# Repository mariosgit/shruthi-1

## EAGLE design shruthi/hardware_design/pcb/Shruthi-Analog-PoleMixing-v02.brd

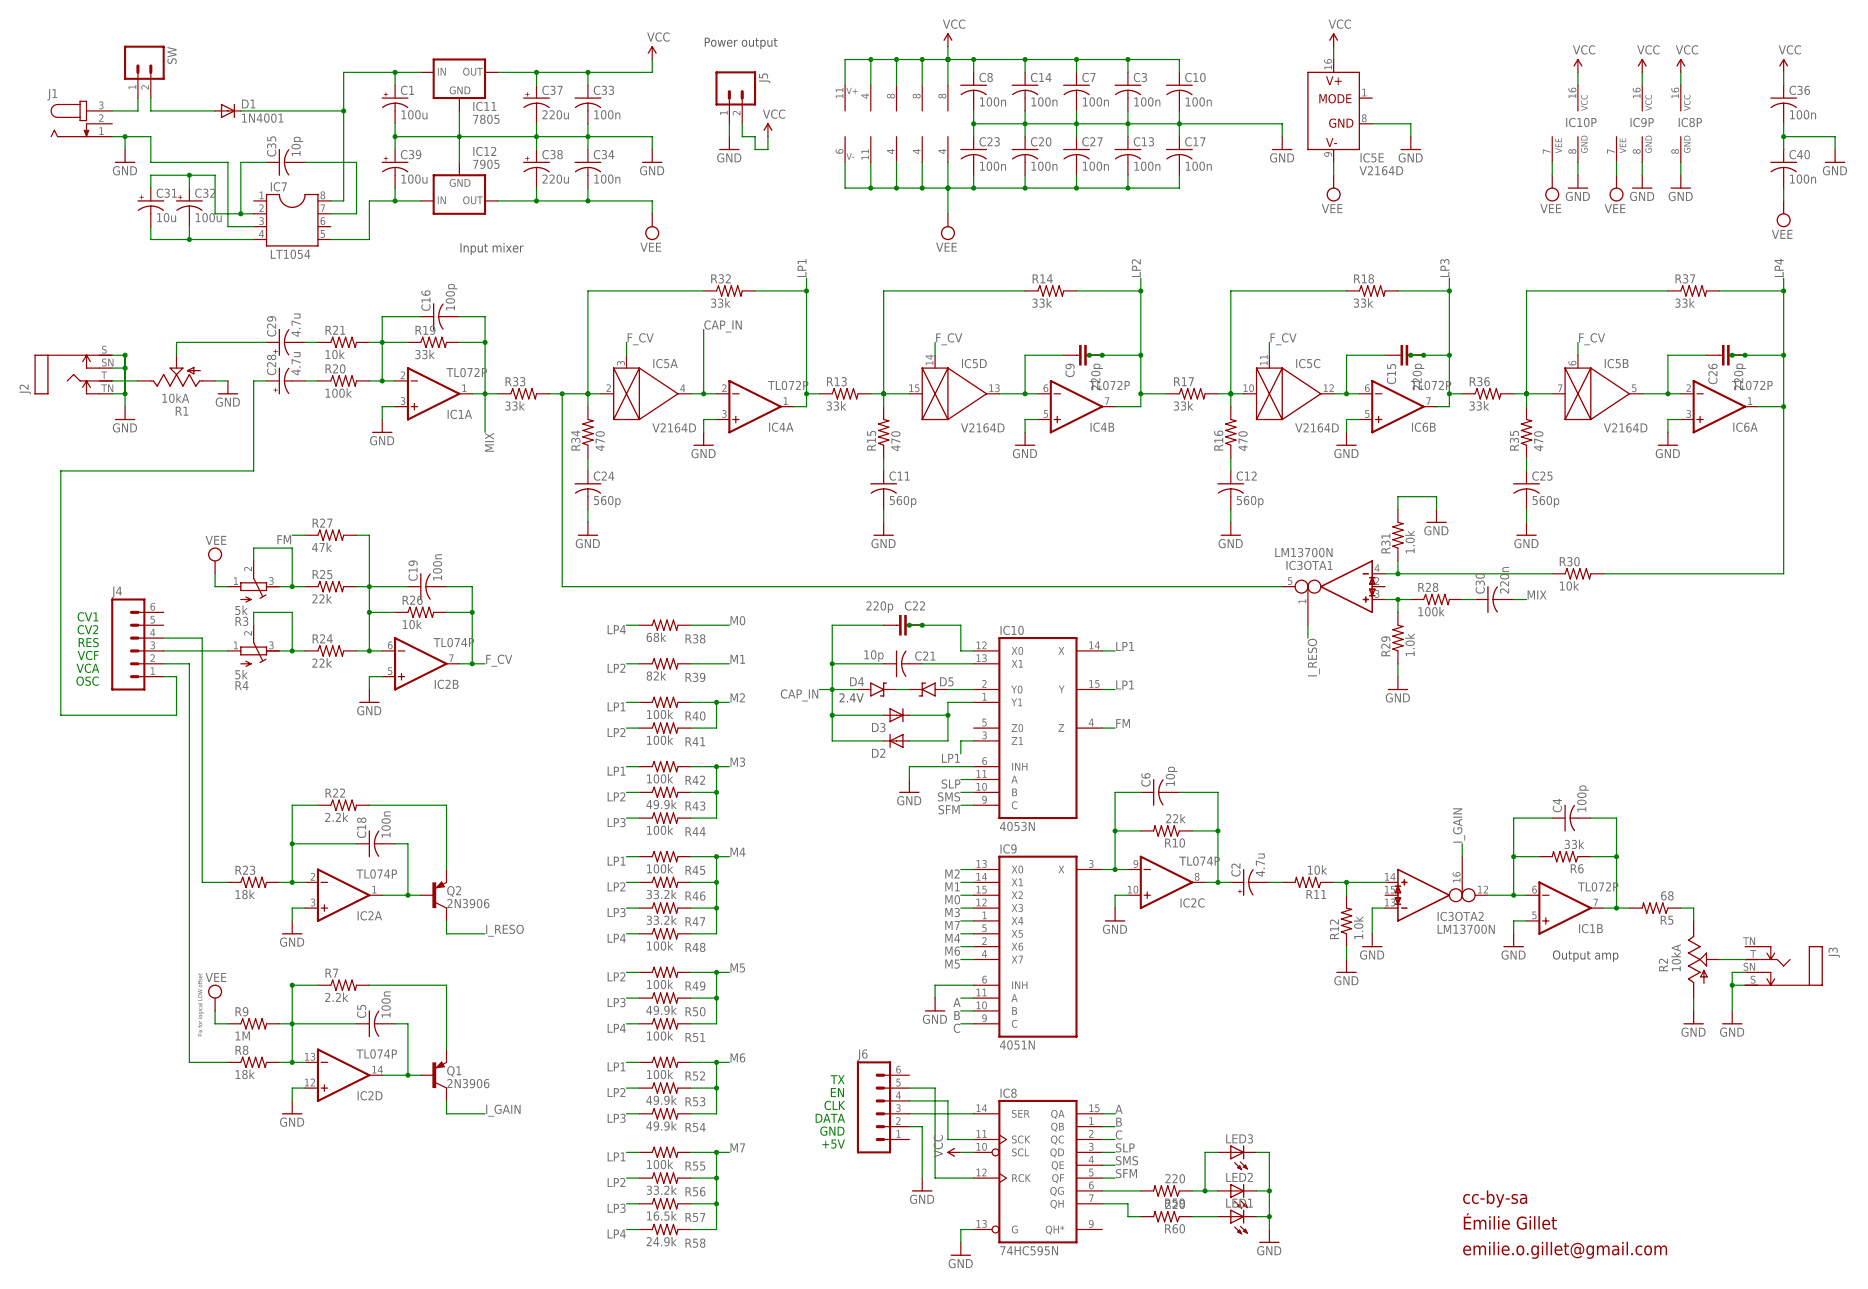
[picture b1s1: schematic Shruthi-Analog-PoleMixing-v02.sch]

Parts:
C1, C39: 100u; E2,5-7
C2, C28, C29: 4.7u; E2,5-6
C3, C5, C7, C8, C10, C13, C14, C17, C18, C19, C20, C23, C27, C33, C34, C36, C40: 100n; C025-025X050
C4, C16: 100p; C025-025X050
C6, C21, C35: 10p; C025-025X050
C9, C15, C22, C26: 220p; C2.5/5-4
C11, C12, C24, C25: 560p; C025-025X050
C30: 220n; C025-025X050
C31: 10u; E2,5-5
C32: 100u; E2,5-6
C37, C38: 220u; E5-10,5
D1: 1N4001; DO41-10
D2, D3: DIODE-D-5; D-5
D4, D5: 1N47XXDO35; D-5
IC1, IC4, IC6: TL072P; DIL08
IC2: TL074P; DIL14
IC3: LM13700N; DIL16
IC5: V2164D; DIL16
IC7: LT1054; DIL08
IC8: 74HC595N; DIL16
IC9: 4051N; DIL16
IC10: 4053N; DIL16
IC11: 7805; 78XXS
IC12: 7905; 79XXS
J1: JACK-PLUG2; SPC4078_BIG_HOLES
J2, J3: MONOSWS; NMJ4HC-S
J4, J6: M06SIP; 1X06
J5: M02PTH; 1X02
LED1, LED2: LED3MM
LED3: LEDCHIP-LED0603; CHIP-LED0603
Q1, Q2: 2N3906; TO92-
R1, R2: 10kA; CABLE_POT_6MM
R3, R4: 5k; RTRIM3296X
R5: 68; 0204/7
R6, R13, R14, R17, R18, R19, R32, R33, R36, R37: 33k; 0204/7
R7, R22: 2.2k; 0204/7
R8, R23: 18k; 0204/7
R9: 1M; 0204/7
R10, R24, R25: 22k; 0204/7
R11, R21, R26, R30: 10k; 0204/7
R12, R29, R31: 1.0k; 0204/7
R15, R16, R34, R35: 470; 0204/7
R20, R28, R40, R41, R42, R44, R45, R48, R49, R51, R52, R55: 100k; 0204/7
R27: 47k; 0204/7
R38: 68k; 0204/7
R39: 82k; 0204/7
R43, R50, R53, R54: 49.9k; 0204/7
R46, R47, R56: 33.2k; 0204/7
R57: 16.5k; 0204/7
R58: 24.9k; 0204/7
R59, R60: 220; 0204/7
SW: M02PTH; 1X02

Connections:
A: IC8.15 (QA), IC9.11 (A)
B: IC8.1 (QB), IC9.10 (B)
C: IC8.2 (QC), IC9.9 (C)
CAP_IN: C21.1, C22.1, D2.C, D3.A, D4.A, IC4.2 (-IN), IC5.4 (OUT)
FM: IC10.4 (Z), R27.1
F_CV: C19.2, IC2.7 (OUT), IC5.3 (CTRL), IC5.6 (CTRL), IC5.11 (CTRL), IC5.14 (CTRL), R26.2
GND: C1.-, C3.2, C7.2, C8.2, C10.2, C11.2, C12.2, C13.1, C14.2, C17.1, C20.1, C23.1, C24.2, C25.2, C27.1, C33.2, C34.1, C36.2, C37.-, C38.+, C39.+, C40.1, IC1.3 (+IN), IC1.5 (+IN), IC2.3 (+IN), IC2.5 (+IN), IC2.10 (+IN), IC2.12 (+IN), IC3.13 (IN_N), IC4.3 (+IN), IC4.5 (+IN), IC5.8 (GND), IC6.3 (+IN), IC6.5 (+IN), IC7.3, IC8.8 (GND), IC8.13 (G), IC9.6 (INH), IC9.8 (GND), IC10.6 (INH), IC10.8 (GND), IC11.GND, IC12.GND, J1.1, J2.S, J2.SN, J2.TN, J3.S, J3.SN, J5.1, J6.2, LED1.K (C), LED2.K (C), LED3.C, R1.A, R2.A, R12.1, R29.1, R31.2
I_GAIN: IC3.16 (I_BIAS), Q1.1 (C)
I_RESO: IC3.1 (I_BIAS), Q2.1 (C)
LP1: IC4.1 (OUT), IC10.3 (Z1), IC10.14 (X), IC10.15 (Y), R13.1, R32.2, R40.1, R42.1, R45.1, R52.1, R55.1
LP2: C9.2, C9.3, IC4.7 (OUT), R14.2, R17.1, R39.1, R41.1, R43.1, R46.1, R49.1, R53.1, R56.1
LP3: C15.2, C15.3, IC6.7 (OUT), R18.2, R36.1, R44.1, R47.1, R50.1, R54.1, R57.1
LP4: C26.2, C26.3, IC6.1 (OUT), R30.2, R37.2, R38.1, R48.1, R51.1, R58.1
M0: IC9.15 (X2), R38.2
M1: IC9.14 (X1), R39.2
M2: IC9.13 (X0), R40.2, R41.2
M3: IC9.12 (X3), R42.2, R43.2, R44.2
M4: IC9.5 (X5), R45.2, R46.2, R47.2, R48.2
M5: IC9.4 (X7), R49.2, R50.2, R51.2
M6: IC9.2 (X6), R52.2, R53.2, R54.2
M7: IC9.1 (X4), R55.2, R56.2, R57.2, R58.2
MIX: C16.2, C30.2, IC1.1 (OUT), R19.2, R33.1
unnamed: C9.1, IC4.6 (-IN), IC5.13 (OUT)
unnamed: C15.1, IC5.12 (OUT), IC6.6 (-IN)
unnamed: IC5.10 (IN), R16.2, R17.2, R18.1
unnamed: C12.1, R16.1
unnamed: C25.1, R35.1
unnamed: C16.1, IC1.2 (-IN), R19.1, R20.2, R21.2
unnamed: IC5.7 (IN), R35.2, R36.2, R37.1
unnamed: C26.1, IC5.5 (OUT), IC6.2 (-IN)
unnamed: C18.2, IC2.1 (OUT), Q2.2 (B)
unnamed: C19.1, IC2.6 (-IN), R24.2, R25.2, R26.1, R27.2
unnamed: R4.2 (S), R4.3 (A), R24.1
unnamed: J4.3, R4.1 (E)
unnamed: J3.T, R2.S
unnamed: IC8.12 (RCK), J6.5
unnamed: C5.2, IC2.14 (OUT), Q1.2 (B)
unnamed: IC3.14 (IN_P), R11.1, R12.2
unnamed: J4.4, R23.1
unnamed: C2.-, R11.2
unnamed: IC3.4 (IN_N), R30.1, R31.1
unnamed: IC3.3 (IN_P), R28.1, R29.2
unnamed: C30.1, R28.2
unnamed: R3.2 (S), R3.3 (A), R25.1
unnamed: D4.C, D5.C
unnamed: R2.E, R5.1
unnamed: C11.1, R15.1
unnamed: C21.2, IC10.13 (X1)
unnamed: IC8.6 (QG), R59.2
unnamed: IC8.11 (SCK), J6.4
unnamed: IC8.14 (SER), J6.3
unnamed: C22.2, C22.3, IC10.12 (X0)
unnamed: IC8.7 (QH), R60.2
unnamed: IC3.5 (OUT), IC5.2 (IN), R32.1, R33.2, R34.2
unnamed: C6.1, IC2.9 (-IN), IC9.3 (X), R10.2
unnamed: C28.+, J4.1
unnamed: C2.+, C6.2, IC2.8 (OUT), R10.1
unnamed: J2.T, R1.E
unnamed: C28.-, R20.1
unnamed: C24.1, R34.1
unnamed: LED2.A, LED3.A, R59.1
unnamed: LED1.A, R60.1
unnamed: IC5.15 (IN), R13.2, R14.1, R15.2
unnamed: J1.3, SW.1
unnamed: J4.2, R8.1
unnamed: C1.+, D1.C, IC7.8, IC11.IN
unnamed: C31.+, C32.+, C35.1, IC7.2
unnamed: C31.-, C32.-, IC7.4
unnamed: C35.2, IC7.7
unnamed: D2.A, D3.C, IC10.1 (Y1)
unnamed: C5.1, IC2.13 (-IN), R7.1, R8.2, R9.2
unnamed: D5.A, IC10.2 (Y0)
unnamed: C18.1, IC2.2 (-IN), R22.1, R23.2
unnamed: C39.-, IC7.5, IC12.IN
unnamed: D1.A, SW.2
unnamed: Q2.3 (E), R22.2
unnamed: C4.2, IC1.7 (OUT), R5.2, R6.1
unnamed: C29.+, R1.S
unnamed: Q1.3 (E), R7.2
unnamed: C4.1, IC1.6 (-IN), IC3.12 (OUT), R6.2
unnamed: C29.-, R21.1
SFM: IC8.5 (QF), IC10.9 (C)
SLP: IC8.3 (QD), IC10.11 (A)
SMS: IC8.4 (QE), IC10.10 (B)
VCC: C3.1, C7.1, C8.1, C10.1, C14.1, C33.1, C36.1, C37.+, IC1.8 (V+), IC2.4 (V+), IC3.11 (V+), IC4.8 (V+), IC5.16 (V+), IC6.8 (V+), IC8.10 (SCL), IC8.16 (VCC), IC9.16 (VCC), IC10.16 (VCC), IC11.OUT, J5.2
VEE: C13.2, C17.2, C20.2, C23.2, C27.2, C34.2, C38.-, C40.2, IC1.4 (V-), IC2.11 (V-), IC3.6 (V-), IC4.4 (V-), IC5.9 (V-), IC6.4 (V-), IC9.7 (VEE), IC10.7 (VEE), IC12.OUT, R3.1 (E), R9.1

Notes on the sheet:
Power output
OSC
VCA
VCF
RES
cc-by-sa
Output amp
CV1
CV2
Input mixer
+5V
GND
DATA
CLK
Fix for logical LOW offset
2.4V
Émilie Gillet
emilie.o.gillet@gmail.com

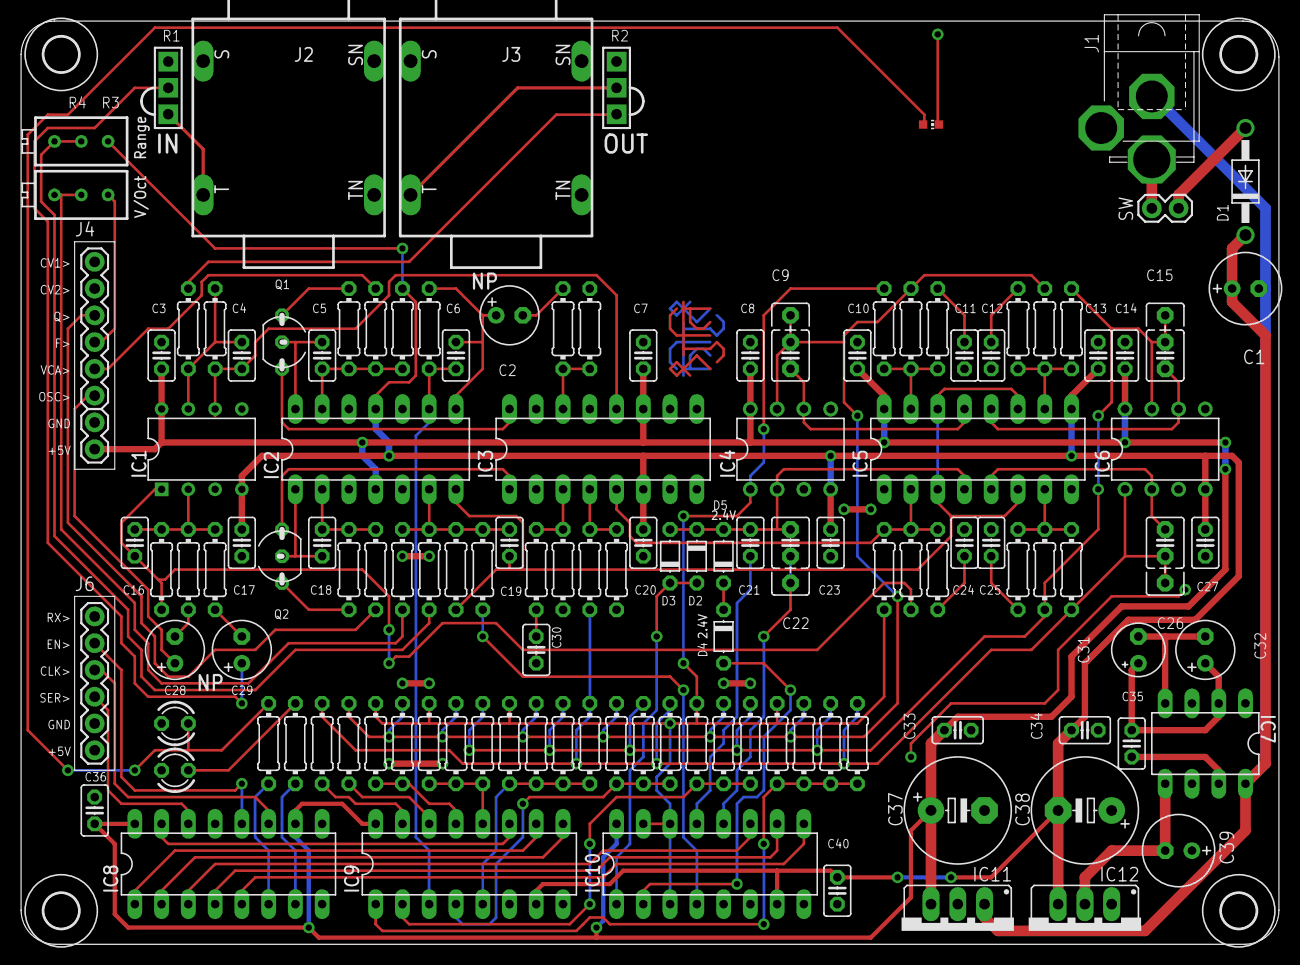
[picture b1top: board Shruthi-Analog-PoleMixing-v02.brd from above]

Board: 2 copper layers, 119.4 x 87.6 mm, 134 parts (0 on the bottom side), 86 nets.

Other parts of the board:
U$1, U$2, U$4, U$5: 3,3
U$3: 4POLE_MISSION

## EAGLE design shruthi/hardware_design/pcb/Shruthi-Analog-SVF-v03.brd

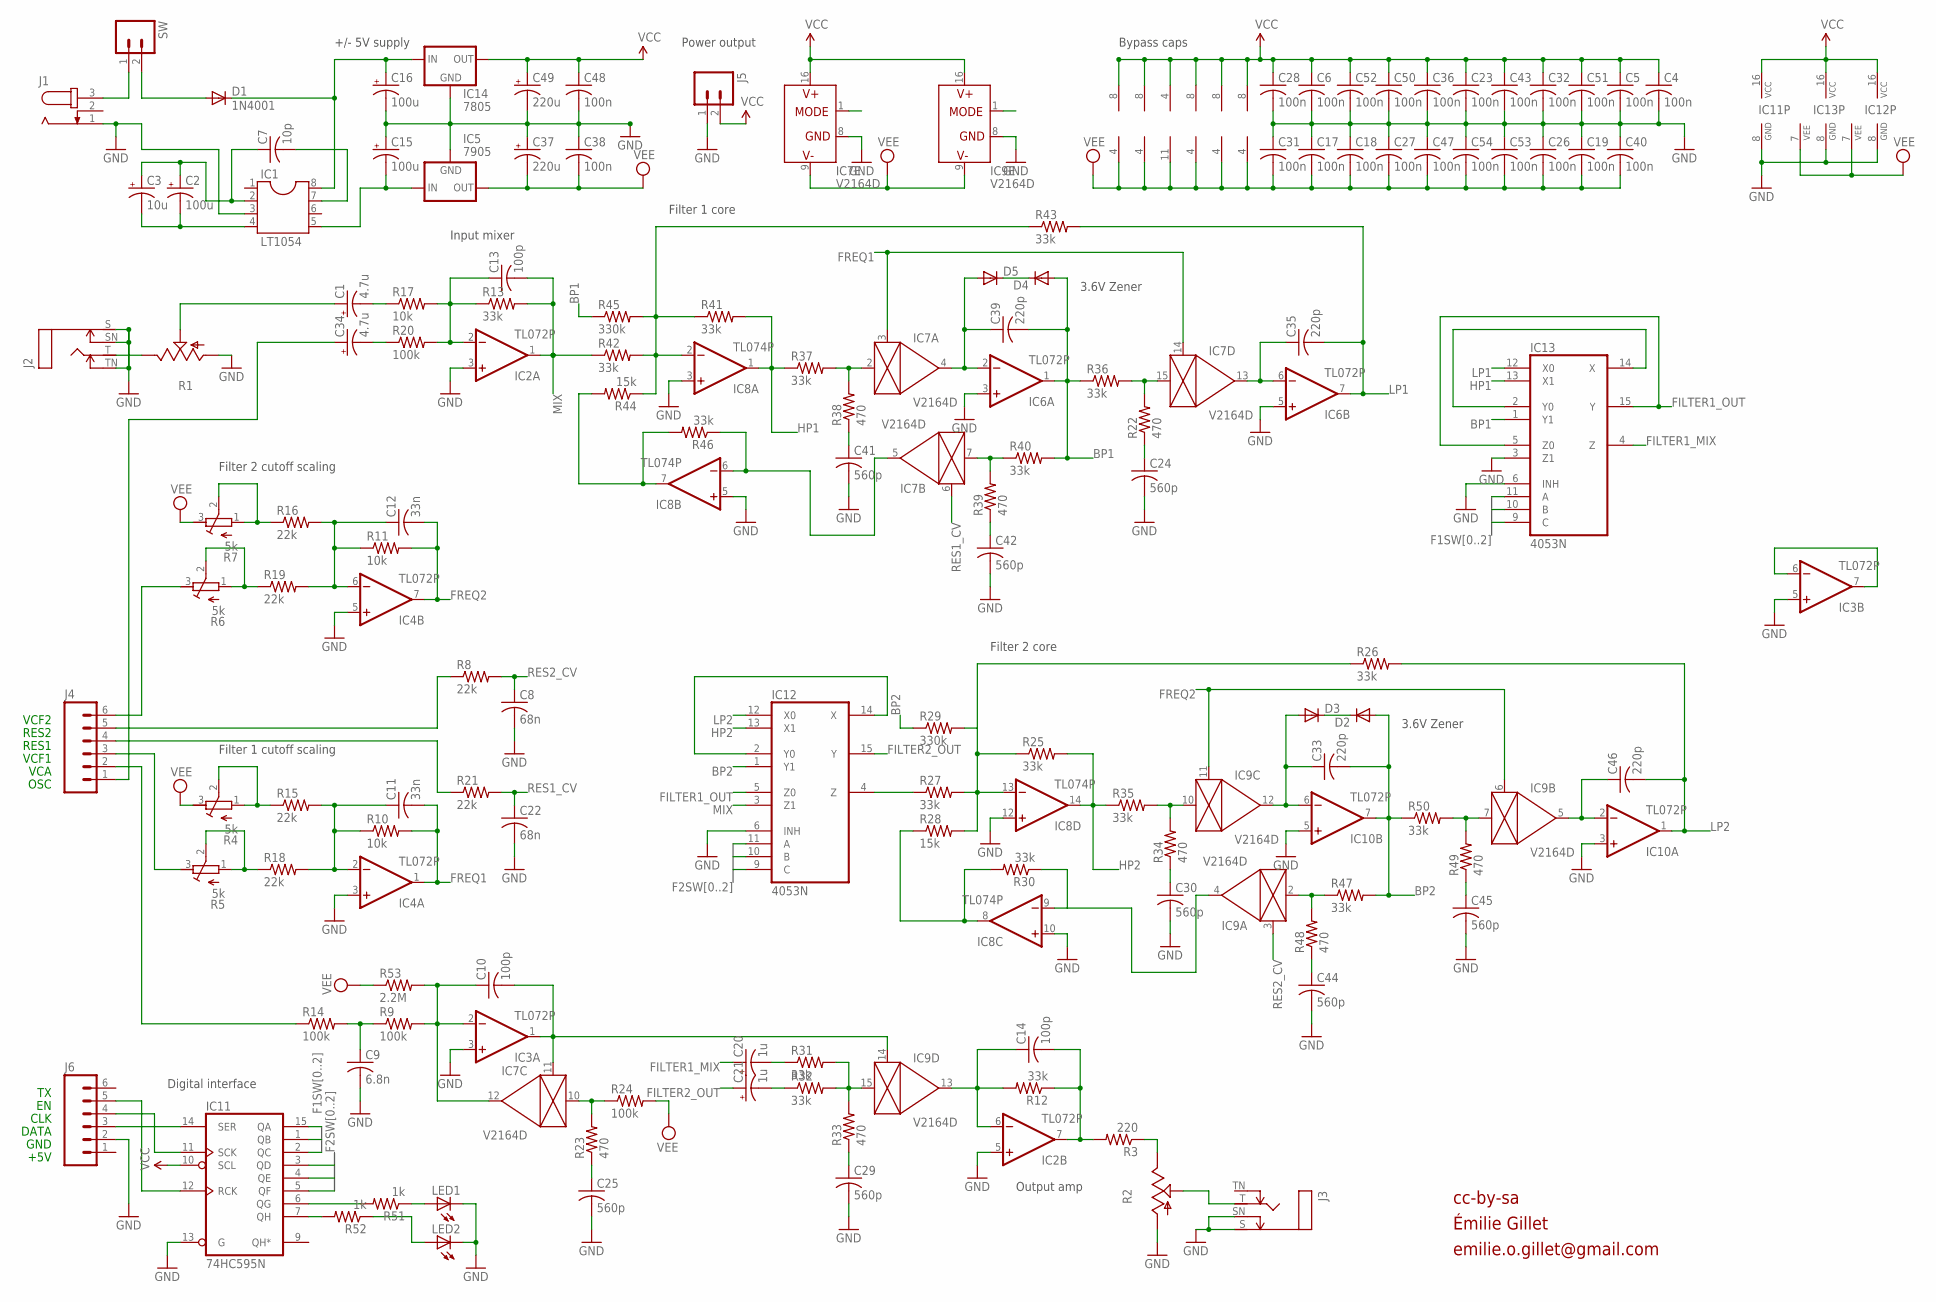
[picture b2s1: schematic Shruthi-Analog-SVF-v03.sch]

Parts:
C1, C34: 4.7u; E2,5-6
C2: 100u; E2,5-6
C3: 10u; E2,5-5
C4, C5, C6, C17, C18, C19, C23, C26, C27, C28, C31, C32, C36, C38, C40, C43, C47, C48, C50, C51, C52, C53, C54: 100n; C025-025X050
C7: 10p; C025-025X050
C8, C22: 68n; C050-025X075
C9: 6.8n; C025-025X050
C10, C13, C14: 100p; C025-025X050
C11, C12: 33n; C050-025X075
C15, C16: 100u; E2,5-7
C20, C21: 1u; E2-5
C24, C25, C29, C30, C41, C42, C44, C45: 560p; C025-025X050
C33, C35, C39, C46: 220p; C025-025X050
C37, C49: 220u; E5-10,5
D1: 1N4001; DO41-10
D2, D3, D4, D5: DIODE-D-5; D-5
IC1: LT1054; DIL08
IC2, IC3, IC4, IC6, IC10: TL072P; DIL08
IC5: 7905; 79XXS
IC7, IC9: V2164D; DIL16
IC8: TL074P; DIL14
IC11: 74HC595N; DIL16
IC12, IC13: 4053N; DIL16
IC14: 7805; 78XXS
J1: JACK-PLUG2; SPC4078_BIG_HOLES
J2, J3: MONOSWS; NMJ4HC-S
J4, J6: M06SIP; 1X06
J5: M02PTH; 1X02
LED1, LED2: LEDCHIP-LED0603; CHIP-LED0603
R1, R2: POT_USCABLED; CABLE_POT_6MM
R3: 220; 0204/7
R4, R5, R6, R7: 5k; RTRIM3296X
R8, R15, R16, R18, R19, R21: 22k; 0204/7
R9, R14, R20, R24: 100k; 0204/7
R10, R11, R17: 10k; 0204/7
R12, R13, R25, R26, R27, R30, R31, R32, R35, R36, R37, R40, R41, R42, R43, R46, R47, R50: 33k; 0204/7
R22, R23, R33, R34, R38, R39, R48, R49: 470; 0204/7
R28, R44: 15k; 0204/7
R29, R45: 330k; 0204/7
R51, R52: 1k; 0204/7
R53: 2.2M; 0204V
SW: M02PTH; 1X02

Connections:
BP1: C39.2, D4.A, IC6.1 (OUT), IC13.1 (Y1), R36.1, R40.2, R45.1
BP2: C33.2, D2.A, IC10.7 (OUT), IC12.1 (Y1), R29.1, R47.2, R50.1
F1SW0: IC11.15 (QA), IC13.9 (C)
F1SW1: IC11.1 (QB), IC13.10 (B)
F1SW2: IC11.2 (QC), IC13.11 (A)
F2SW0: IC11.3 (QD), IC12.9 (C)
F2SW1: IC11.4 (QE), IC12.10 (B)
F2SW2: IC11.5 (QF), IC12.11 (A)
FILTER1_MIX: C20.+, IC13.4 (Z)
FILTER1_OUT: IC12.5 (Z0), IC13.5 (Z0), IC13.15 (Y)
FILTER2_OUT: C21.+, IC12.15 (Y)
FREQ1: C11.2, IC4.1 (OUT), IC7.3 (CTRL), IC7.14 (CTRL), R10.2
FREQ2: C12.2, IC4.7 (OUT), IC9.6 (CTRL), IC9.11 (CTRL), R11.2
GND: C4.2, C5.2, C6.2, C8.2, C9.2, C15.+, C16.-, C17.1, C18.1, C19.1, C22.2, C23.2, C24.2, C25.2, C26.1, C27.1, C28.2, C29.2, C30.2, C31.1, C32.2, C36.2, C37.+, C38.1, C40.1, C41.2, C42.2, C43.2, C44.2, C45.2, C47.1, C48.2, C49.-, C50.2, C51.2, C52.2, C53.1, C54.1, IC1.3, IC2.3 (+IN), IC2.5 (+IN), IC3.3 (+IN), IC3.5 (+IN), IC4.3 (+IN), IC4.5 (+IN), IC5.GND, IC6.3 (+IN), IC6.5 (+IN), IC7.8 (GND), IC8.3 (+IN), IC8.5 (+IN), IC8.10 (+IN), IC8.12 (+IN), IC9.8 (GND), IC10.3 (+IN), IC10.5 (+IN), IC11.8 (GND), IC11.13 (G), IC12.6 (INH), IC12.8 (GND), IC13.3 (Z1), IC13.6 (INH), IC13.8 (GND), IC14.GND, J1.1, J2.S, J2.SN, J2.TN, J3.S, J3.SN, J5.1, J6.2, LED1.C, LED2.C, R1.A, R2.A
HP1: IC8.1 (OUT), IC13.13 (X1), R37.1, R41.2
HP2: IC8.14 (OUT), IC12.13 (X1), R25.2, R35.1
LP1: C35.2, IC6.7 (OUT), IC13.12 (X0), R43.2
LP2: C46.2, IC10.1 (OUT), IC12.12 (X0), R26.2
MIX: C13.2, IC2.1 (OUT), IC12.3 (Z1), R13.2, R42.1
unnamed: C2.+, C3.+, C7.1, IC1.2
unnamed: C12.1, IC4.6 (-IN), R11.1, R16.2, R19.2
unnamed: J1.3, SW.1
unnamed: C16.+, D1.C, IC1.8, IC14.IN
unnamed: C2.-, C3.-, IC1.4
unnamed: C13.1, IC2.2 (-IN), R13.1, R17.2, R20.2
unnamed: R6.1 (E), R6.2 (S), R19.1
unnamed: J4.6, R6.3 (A)
unnamed: R7.1 (E), R7.2 (S), R16.1
unnamed: IC7.10 (IN), R23.2, R24.1
unnamed: C10.1, IC3.2 (-IN), IC7.12 (OUT), R9.2, R53.2
unnamed: IC8.2 (-IN), R41.1, R42.2, R43.1, R44.1, R45.2
unnamed: IC11.12 (RCK), J6.5
unnamed: IC11.14 (SER), J6.3
unnamed: IC11.6 (QG), R51.2
unnamed: IC11.11 (SCK), J6.4
unnamed: C24.1, R22.1
unnamed: IC8.13 (-IN), R25.1, R26.1, R27.2, R28.2, R29.2
unnamed: C39.1, D5.A, IC6.2 (-IN), IC7.4 (OUT)
unnamed: C33.1, D3.A, IC9.12 (OUT), IC10.6 (-IN)
unnamed: IC7.7 (IN), R39.2, R40.1
unnamed: C9.1, R9.1, R14.2
unnamed: IC8.8 (OUT), R28.1, R30.2
unnamed: IC9.2 (IN), R47.1, R48.2
unnamed: R2.E, R3.1
unnamed: IC7.15 (IN), R22.2, R36.2
unnamed: C42.1, R39.1
unnamed: C35.1, IC6.6 (-IN), IC7.13 (OUT)
unnamed: IC7.2 (IN), R37.2, R38.2
unnamed: C41.1, R38.1
unnamed: IC7.5 (OUT), IC8.6 (-IN), R46.1
unnamed: LED1.A, R51.1
unnamed: D2.C, D3.C
unnamed: IC9.7 (IN), R49.2, R50.2
unnamed: C34.+, J4.1
unnamed: C7.2, IC1.7
unnamed: IC8.9 (-IN), IC9.4 (OUT), R30.1
unnamed: J2.T, R1.E
unnamed: C34.-, R20.1
unnamed: C11.1, IC4.2 (-IN), R10.1, R15.2, R18.2
unnamed: R5.1 (E), R5.2 (S), R18.1
unnamed: J4.3, R5.3 (A)
unnamed: R4.1 (E), R4.2 (S), R15.1
unnamed: C46.1, IC9.5 (OUT), IC10.2 (-IN)
unnamed: J4.2, R14.1
unnamed: C45.1, R49.1
unnamed: J3.T, R2.S
unnamed: IC8.7 (OUT), R44.2, R46.2
unnamed: C44.1, R48.1
unnamed: IC9.10 (IN), R34.2, R35.2
unnamed: C30.1, R34.1
unnamed: LED2.A, R52.1
unnamed: IC11.7 (QH), R52.2
unnamed: D4.C, D5.C
unnamed: C10.2, IC3.1 (OUT), IC7.11 (CTRL), IC9.14 (CTRL)
unnamed: C20.-, R31.1
unnamed: C15.-, IC1.5, IC5.IN
unnamed: D1.A, SW.2
unnamed: C21.-, R32.1
unnamed: IC3.6 (-IN), IC3.7 (OUT)
unnamed: IC13.2 (Y0), IC13.14 (X)
unnamed: C14.2, IC2.7 (OUT), R3.2, R12.1
unnamed: C25.1, R23.1
unnamed: C29.1, R33.1
unnamed: C1.+, R1.S
unnamed: IC9.15 (IN), R31.2, R32.2, R33.2
unnamed: J4.4, R21.1
unnamed: C14.1, IC2.6 (-IN), IC9.13 (OUT), R12.2
unnamed: C1.-, R17.1
unnamed: J4.5, R8.1
unnamed: IC12.2 (Y0), IC12.14 (X)
unnamed: IC12.4 (Z), R27.1
RES1_CV: C22.1, IC7.6 (CTRL), R21.2
RES2_CV: C8.1, IC9.3 (CTRL), R8.2
VCC: C4.1, C5.1, C6.1, C23.1, C28.1, C32.1, C36.1, C43.1, C48.1, C49.+, C50.1, C51.1, C52.1, IC2.8 (V+), IC3.8 (V+), IC4.8 (V+), IC6.8 (V+), IC7.16 (V+), IC8.4 (V+), IC9.16 (V+), IC10.8 (V+), IC11.10 (SCL), IC11.16 (VCC), IC12.16 (VCC), IC13.16 (VCC), IC14.OUT, J5.2
VEE: C17.2, C18.2, C19.2, C26.2, C27.2, C31.2, C37.-, C38.2, C40.2, C47.2, C53.2, C54.2, IC2.4 (V-), IC3.4 (V-), IC4.4 (V-), IC5.OUT, IC6.4 (V-), IC7.9 (V-), IC8.11 (V-), IC9.9 (V-), IC10.4 (V-), IC12.7 (VEE), IC13.7 (VEE), R4.3 (A), R7.3 (A), R24.2, R53.1

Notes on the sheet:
Power output
OSC
VCA
VCF1
RES1
Input mixer
Filter 1 cutoff scaling
cc-by-sa
+/- 5V supply
Bypass caps
Output amp
VCF2
RES2
+5V
GND
DATA
CLK
Digital interface
Filter 2 cutoff scaling
Filter 1 core
Filter 2 core
3.6V Zener
Émilie Gillet
emilie.o.gillet@gmail.com

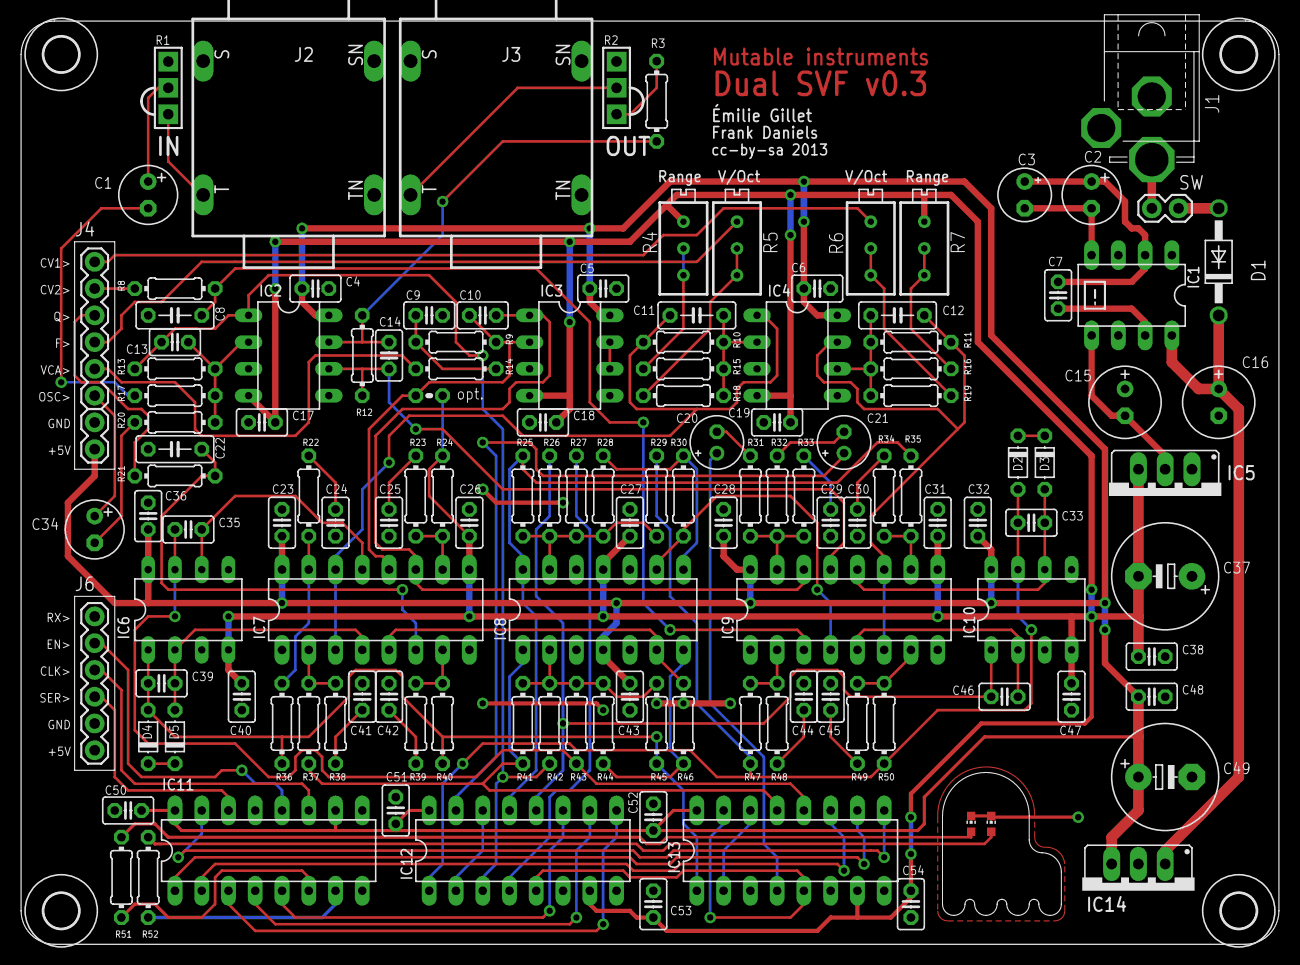
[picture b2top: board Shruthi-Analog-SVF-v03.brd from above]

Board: 2 copper layers, 119.4 x 87.6 mm, 139 parts (0 on the bottom side), 95 nets.

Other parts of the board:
U$1, U$2, U$3, U$4: 3,3

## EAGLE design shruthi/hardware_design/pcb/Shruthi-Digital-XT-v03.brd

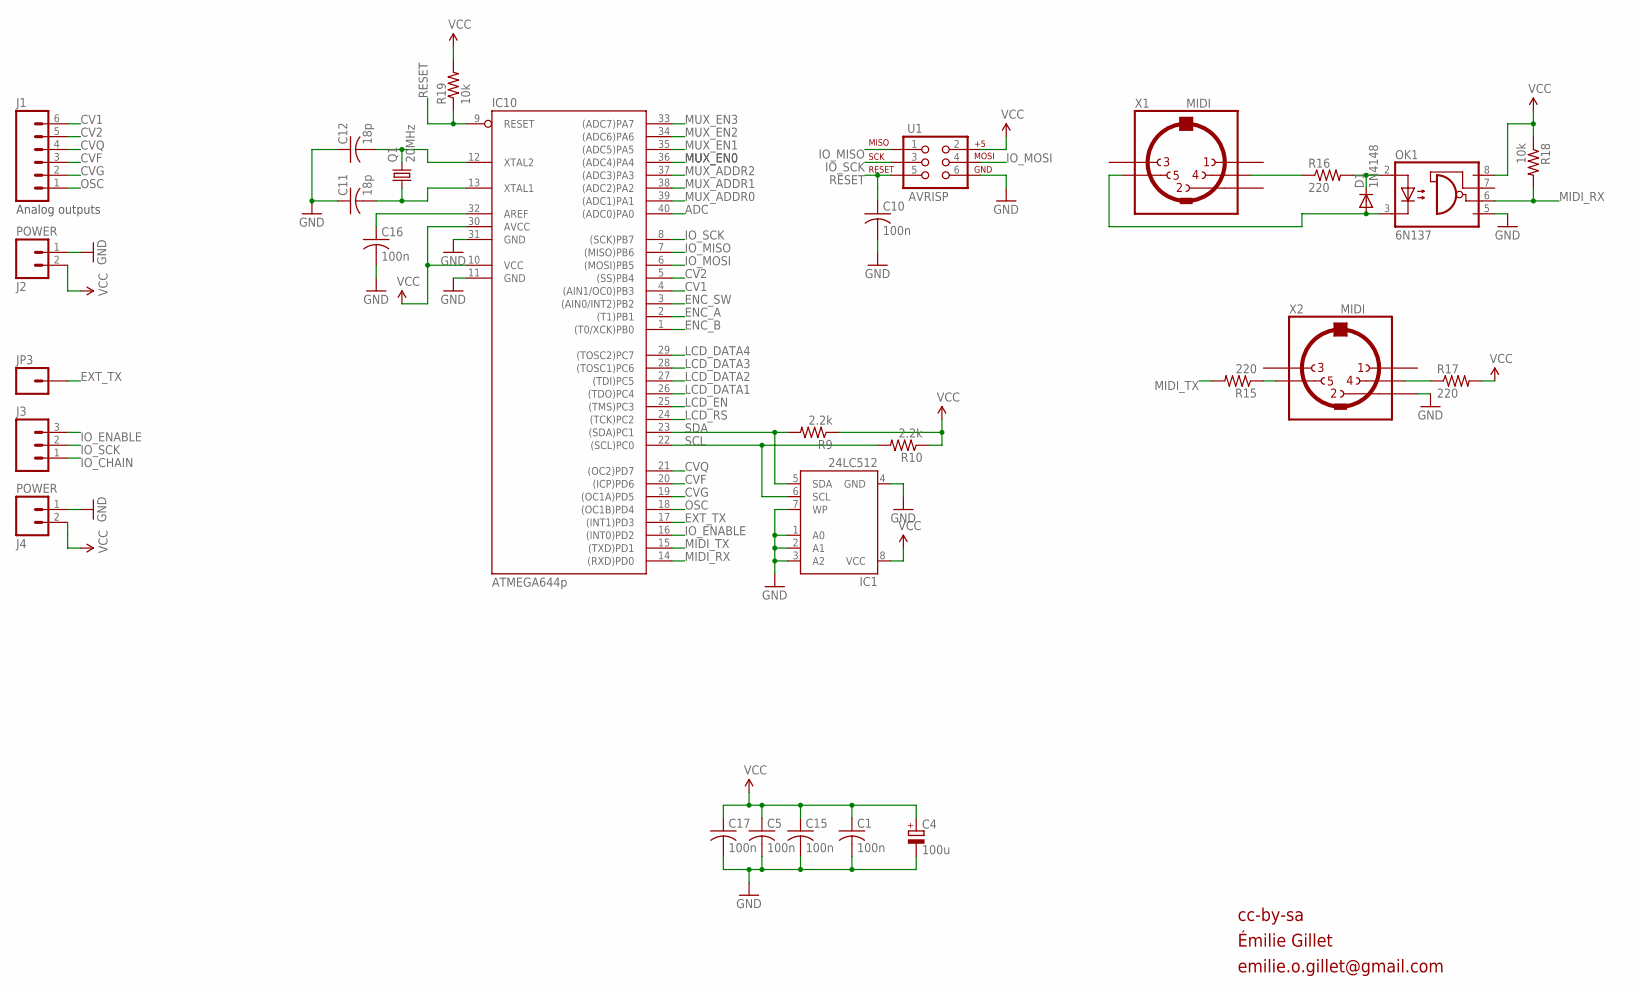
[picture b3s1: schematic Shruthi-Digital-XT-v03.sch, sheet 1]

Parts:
C1, C5, C10, C15, C16, C17: 100n; C025-024X044
C4: 100u; E2,5-7
C11, C12: 18p; C025-024X044
D1: 1N4148; D-5
IC1: 24LC512; DIL08
IC10: ATMEGA644p; DIL40
J1: M06SIP; 1X06
J2, J4: POWER; 1X02
J3: M03PTH; 1X03
JP3: M01PTH; 1X01
OK1: 6N137; DIL08
Q1: 20MHz; HC49U-V
R9, R10: 2.2k; 0204/7
R15, R16, R17: 220; 0204/7
R18, R19: 10k; 0204/7
U1: AVRISP; 2X3
X1, X2: MIDI; MAB5SH

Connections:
ADC: IC10.40 ((ADC0)PA0); also elsewhere on the board
CV1: IC10.4 ((AIN1/OC0)PB3), J1.6
CV2: IC10.5 ((SS)PB4), J1.5
CVF: IC10.20 ((ICP)PD6), J1.3
CVG: IC10.19 ((OC1A)PD5), J1.2
CVQ: IC10.21 ((OC2)PD7), J1.4
ENC_A: IC10.2 ((T1)PB1); also elsewhere on the board
ENC_B: IC10.1 ((T0/XCK)PB0); also elsewhere on the board
ENC_SW: IC10.3 ((AIN0/INT2)PB2); also elsewhere on the board
EXT_TX: IC10.17 ((INT1)PD3), JP3.1
GND: C1.2, C4.-, C5.2, C10.2, C11.1, C12.1, C15.2, C16.2, C17.2, IC1.1 (A0), IC1.2 (A1), IC1.3 (A2), IC1.4 (GND), IC1.7 (WP), IC10.11 (GND), IC10.31 (GND), J2.1, J4.1, OK1.5 (GND), U1.6, X2.2; also elsewhere on the board
IO_CHAIN: J3.1; also elsewhere on the board
IO_ENABLE: IC10.16 ((INT0)PD2), J3.3; also elsewhere on the board
IO_MISO: IC10.7 ((MISO)PB6), U1.1; also elsewhere on the board
IO_MOSI: IC10.6 ((MOSI)PB5), U1.4; also elsewhere on the board
IO_SCK: IC10.8 ((SCK)PB7), J3.2, U1.3; also elsewhere on the board
LCD_DATA1: IC10.26 ((TDO)PC4); also elsewhere on the board
LCD_DATA2: IC10.27 ((TDI)PC5); also elsewhere on the board
LCD_DATA3: IC10.28 ((TOSC1)PC6); also elsewhere on the board
LCD_DATA4: IC10.29 ((TOSC2)PC7); also elsewhere on the board
LCD_EN: IC10.25 ((TMS)PC3); also elsewhere on the board
LCD_RS: IC10.24 ((TCK)PC2); also elsewhere on the board
MIDI_RX: IC10.14 ((RXD)PD0), OK1.6 (VO), R18.2
MIDI_TX: IC10.15 ((TXD)PD1), R15.2
MUX_ADDR0: IC10.39 ((ADC1)PA1); also elsewhere on the board
MUX_ADDR1: IC10.38 ((ADC2)PA2); also elsewhere on the board
MUX_ADDR2: IC10.37 ((ADC3)PA3); also elsewhere on the board
MUX_EN0: IC10.36 ((ADC4)PA4); also elsewhere on the board
MUX_EN1: IC10.35 ((ADC5)PA5); also elsewhere on the board
MUX_EN2: IC10.34 ((ADC6)PA6); also elsewhere on the board
MUX_EN3: IC10.33 ((ADC7)PA7); also elsewhere on the board
unnamed: R15.1, X2.5
unnamed: C16.1, IC10.32 (AREF)
unnamed: D1.C, OK1.2 (A), R16.2
unnamed: R17.1, X2.4
unnamed: R16.1, X1.4
unnamed: D1.A, OK1.3 (C), X1.5
unnamed: C11.2, IC10.13 (XTAL1), Q1.1
unnamed: C12.2, IC10.12 (XTAL2), Q1.2
OSC: IC10.18 ((OC1B)PD4), J1.1
RESET: C10.1, IC10.9 (RESET), R19.1, U1.5
SCL: IC1.6 (SCL), IC10.22 ((SCL)PC0), R10.2
SDA: IC1.5 (SDA), IC10.23 ((SDA)PC1), R9.2
VCC: C1.1, C4.+, C5.1, C15.1, C17.1, IC1.8 (VCC), IC10.10 (VCC), IC10.30 (AVCC), J2.2, J4.2, OK1.8 (VCC), R9.1, R10.1, R17.2, R18.1, R19.2, U1.2; also elsewhere on the board

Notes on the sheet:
Analog outputs
cc-by-sa
Émilie Gillet
emilie.o.gillet@gmail.com

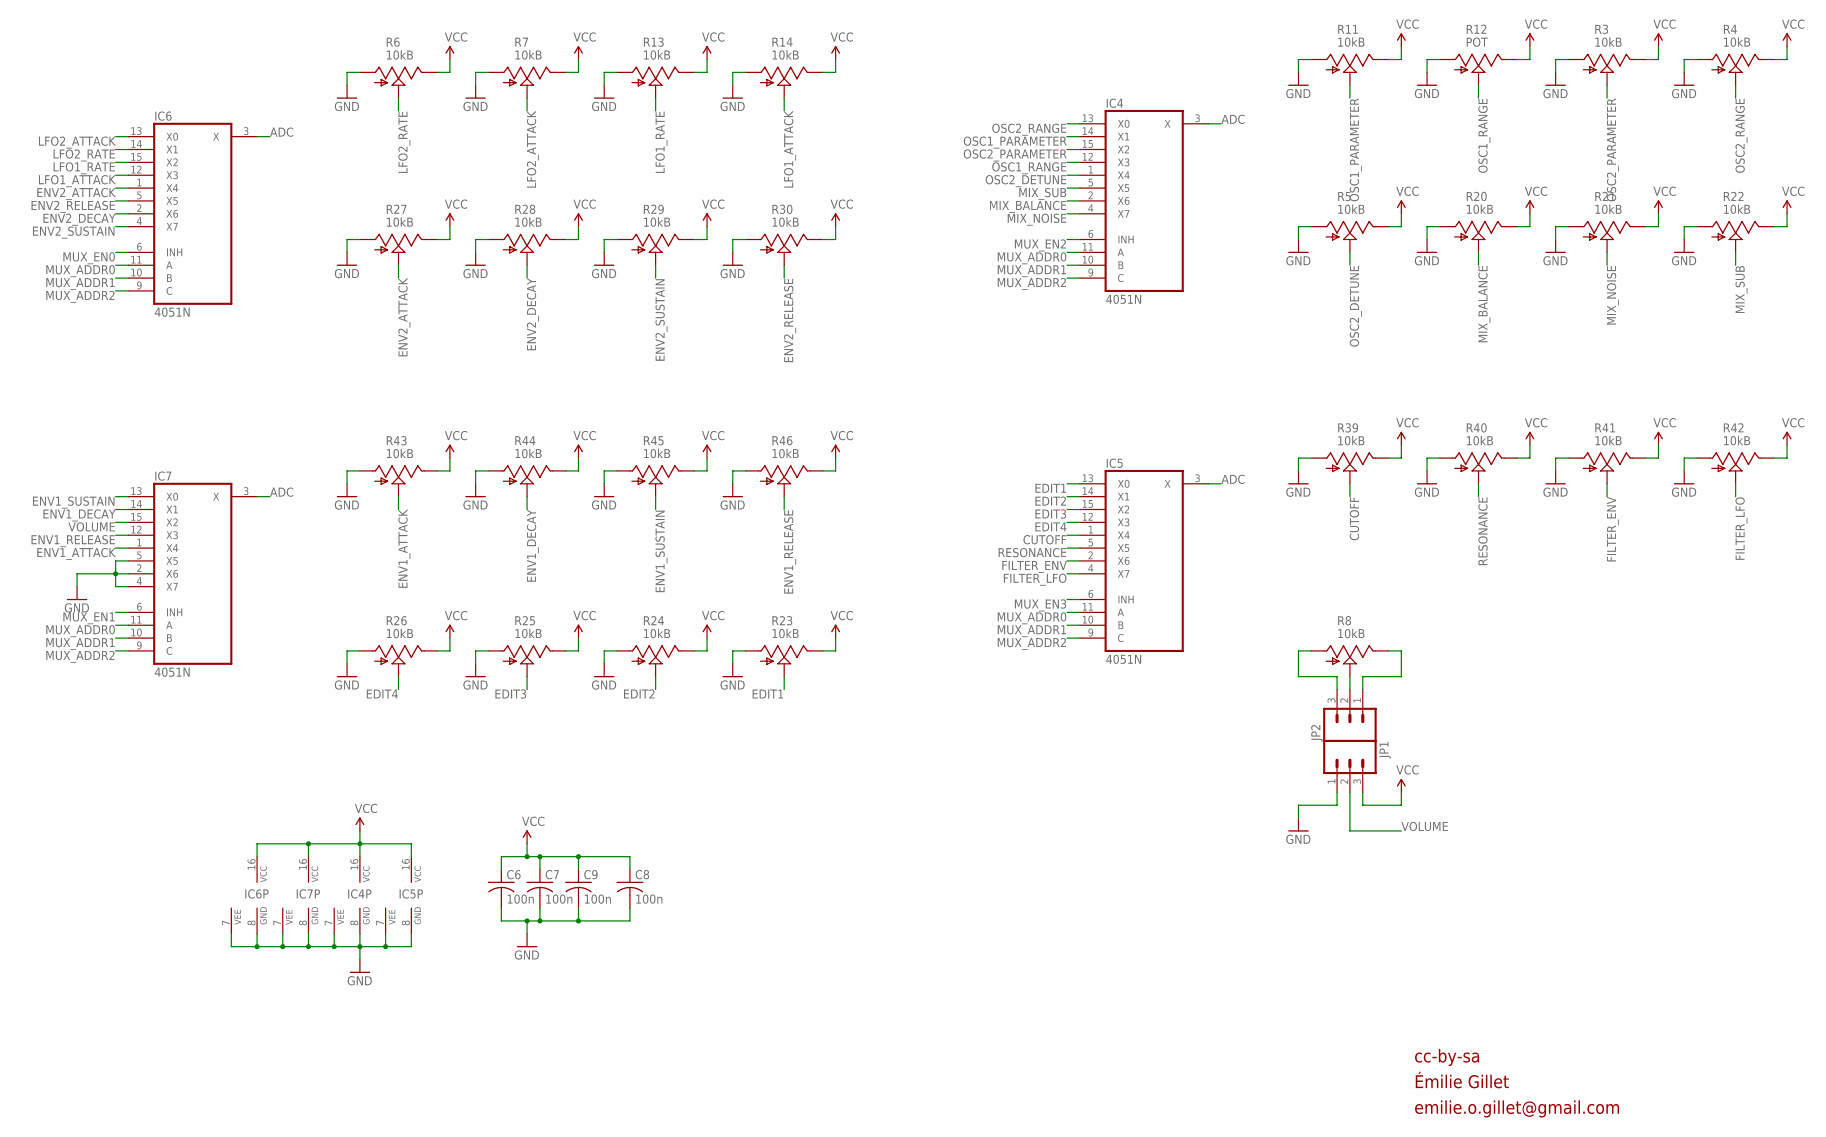
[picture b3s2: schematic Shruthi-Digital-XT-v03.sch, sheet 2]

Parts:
C6, C7, C8, C9: 100n; C025-024X044
IC4, IC5, IC6, IC7: 4051N; DIL16
JP1, JP2: M03PTH; 1X03
R3, R4, R5, R6, R7, R8, R11, R13, R14, R20, R21, R22, R23, R24, R25, R26, R27, R28, R29, R30, R39, R40, R41, R42, R43, R44, R45, R46: 10kB; ALPS_POT_VERTICAL
R12: POT; ALPS_POT_VERTICAL

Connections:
ADC: IC4.3 (X), IC5.3 (X), IC6.3 (X), IC7.3 (X); also elsewhere on the board
CUTOFF: IC5.1 (X4), R39.P$2 (S)
EDIT1: IC5.13 (X0), R23.P$2 (S)
EDIT2: IC5.14 (X1), R24.P$2 (S)
EDIT3: IC5.15 (X2), R25.P$2 (S)
EDIT4: IC5.12 (X3), R26.P$2 (S)
ENV1_ATTACK: IC7.1 (X4), R43.P$2 (S)
ENV1_DECAY: IC7.14 (X1), R44.P$2 (S)
ENV1_RELEASE: IC7.12 (X3), R46.P$2 (S)
ENV1_SUSTAIN: IC7.13 (X0), R45.P$2 (S)
ENV2_ATTACK: IC6.1 (X4), R27.P$2 (S)
ENV2_DECAY: IC6.2 (X6), R28.P$2 (S)
ENV2_RELEASE: IC6.5 (X5), R30.P$2 (S)
ENV2_SUSTAIN: IC6.4 (X7), R29.P$2 (S)
FILTER_ENV: IC5.2 (X6), R41.P$2 (S)
FILTER_LFO: IC5.4 (X7), R42.P$2 (S)
GND: C6.2, C7.2, C8.2, C9.2, IC4.7 (VEE), IC4.8 (GND), IC5.7 (VEE), IC5.8 (GND), IC6.7 (VEE), IC6.8 (GND), IC7.2 (X6), IC7.4 (X7), IC7.5 (X5), IC7.7 (VEE), IC7.8 (GND), JP1.1, R3.P$3 (A), R4.P$3 (A), R5.P$3 (A), R6.P$3 (A), R7.P$3 (A), R11.P$3 (A), R12.P$3 (A), R13.P$3 (A), R14.P$3 (A), R20.P$3 (A), R21.P$3 (A), R22.P$3 (A), R23.P$3 (A), R24.P$3 (A), R25.P$3 (A), R26.P$3 (A), R27.P$3 (A), R28.P$3 (A), R29.P$3 (A), R30.P$3 (A), R39.P$3 (A), R40.P$3 (A), R41.P$3 (A), R42.P$3 (A), R43.P$3 (A), R44.P$3 (A), R45.P$3 (A), R46.P$3 (A); also elsewhere on the board
LFO1_ATTACK: IC6.12 (X3), R14.P$2 (S)
LFO1_RATE: IC6.15 (X2), R13.P$2 (S)
LFO2_ATTACK: IC6.13 (X0), R7.P$2 (S)
LFO2_RATE: IC6.14 (X1), R6.P$2 (S)
MIX_BALANCE: IC4.2 (X6), R20.P$2 (S)
MIX_NOISE: IC4.4 (X7), R21.P$2 (S)
MIX_SUB: IC4.5 (X5), R22.P$2 (S)
MUX_ADDR0: IC4.11 (A), IC5.11 (A), IC6.11 (A), IC7.11 (A); also elsewhere on the board
MUX_ADDR1: IC4.10 (B), IC5.10 (B), IC6.10 (B), IC7.10 (B); also elsewhere on the board
MUX_ADDR2: IC4.9 (C), IC5.9 (C), IC6.9 (C), IC7.9 (C); also elsewhere on the board
MUX_EN0: IC6.6 (INH); also elsewhere on the board
MUX_EN1: IC7.6 (INH); also elsewhere on the board
MUX_EN2: IC4.6 (INH); also elsewhere on the board
MUX_EN3: IC5.6 (INH); also elsewhere on the board
unnamed: JP2.3, R8.P$3 (A)
unnamed: JP2.1, R8.P$1 (E)
unnamed: JP2.2, R8.P$2 (S)
OSC1_PARAMETER: IC4.14 (X1), R11.P$2 (S)
OSC1_RANGE: IC4.12 (X3), R12.P$2 (S)
OSC2_DETUNE: IC4.1 (X4), R5.P$2 (S)
OSC2_PARAMETER: IC4.15 (X2), R3.P$2 (S)
OSC2_RANGE: IC4.13 (X0), R4.P$2 (S)
RESONANCE: IC5.5 (X5), R40.P$2 (S)
VCC: C6.1, C7.1, C8.1, C9.1, IC4.16 (VCC), IC5.16 (VCC), IC6.16 (VCC), IC7.16 (VCC), JP1.3, R3.P$1 (E), R4.P$1 (E), R5.P$1 (E), R6.P$1 (E), R7.P$1 (E), R11.P$1 (E), R12.P$1 (E), R13.P$1 (E), R14.P$1 (E), R20.P$1 (E), R21.P$1 (E), R22.P$1 (E), R23.P$1 (E), R24.P$1 (E), R25.P$1 (E), R26.P$1 (E), R27.P$1 (E), R28.P$1 (E), R29.P$1 (E), R30.P$1 (E), R39.P$1 (E), R40.P$1 (E), R41.P$1 (E), R42.P$1 (E), R43.P$1 (E), R44.P$1 (E), R45.P$1 (E), R46.P$1 (E); also elsewhere on the board
VOLUME: IC7.15 (X2), JP1.2

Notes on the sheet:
cc-by-sa
Émilie Gillet
emilie.o.gillet@gmail.com
